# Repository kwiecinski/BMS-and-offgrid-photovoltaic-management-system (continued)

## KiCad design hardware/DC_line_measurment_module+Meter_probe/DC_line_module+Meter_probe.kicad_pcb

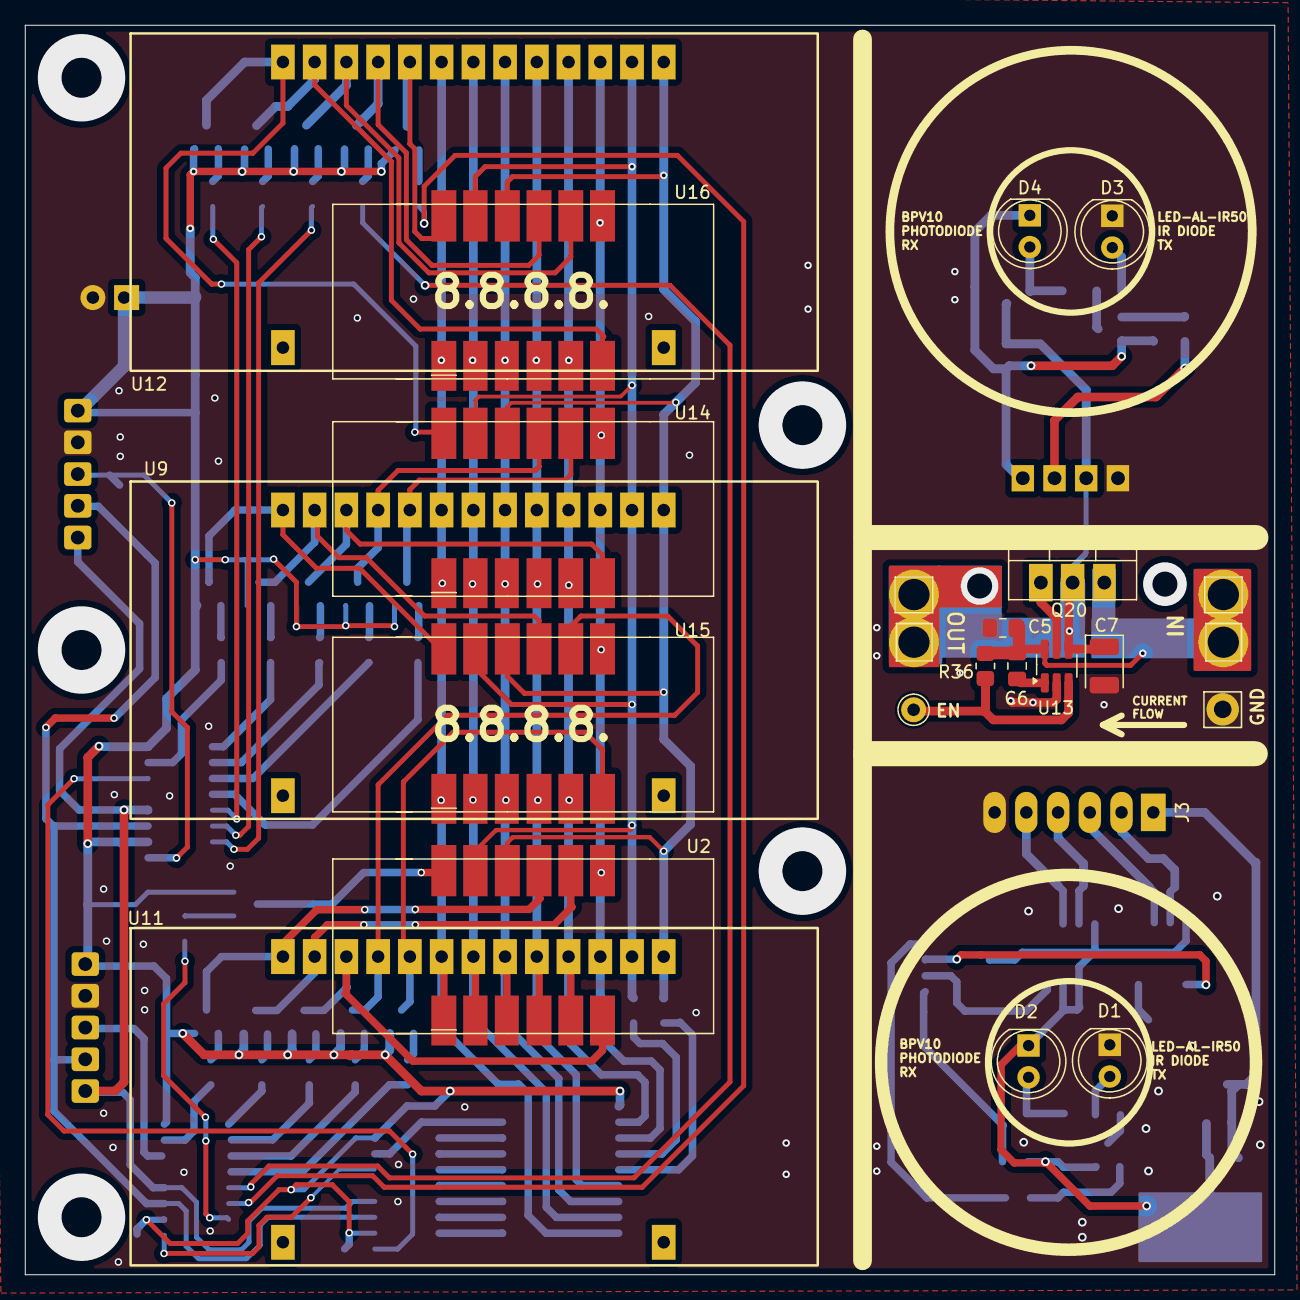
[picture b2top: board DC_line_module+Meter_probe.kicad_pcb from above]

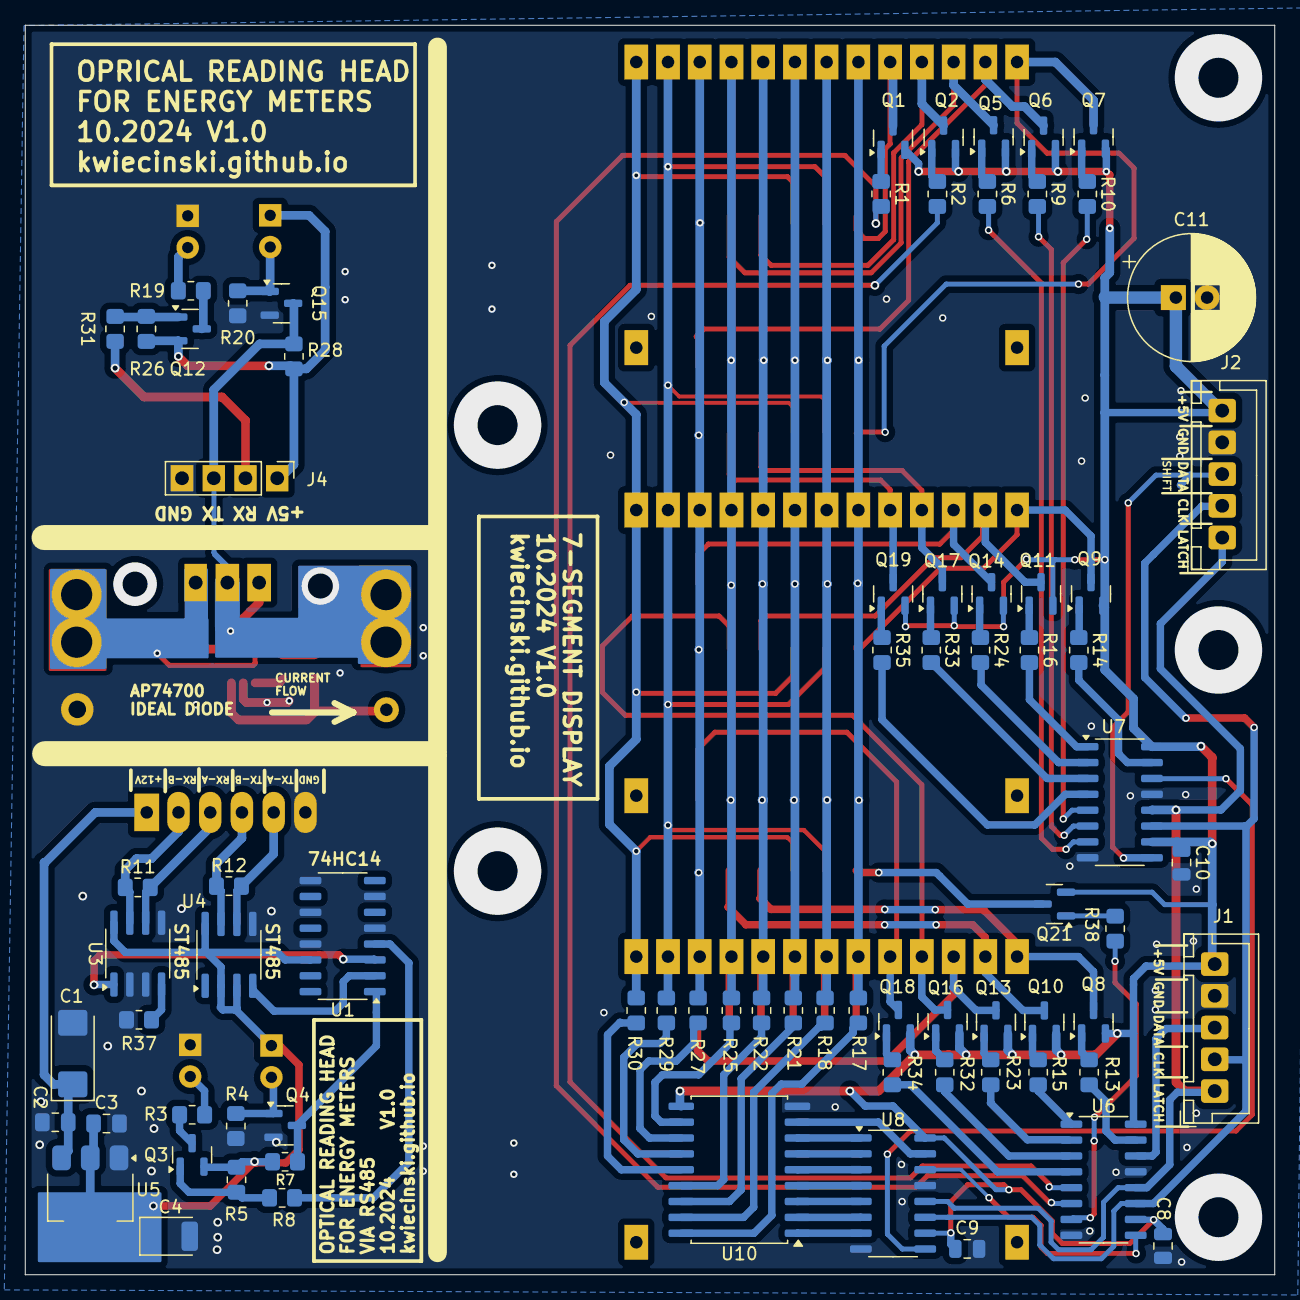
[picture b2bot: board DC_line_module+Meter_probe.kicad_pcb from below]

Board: 2 copper layers, 100.0 x 100.0 mm, 100 parts (76 on the bottom side), 106 nets.

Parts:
C1: 100u; CP_EIA-6032-28_Kemet-C
C2, C3, C5, C6: 100n; C_0805_2012Metric_Pad1.18x1.45mm_HandSolder
C4, C7: 22u; CP_EIA-3528-21_Kemet-B
C8, C9, C10: 100n; C_0805_2012Metric
C11: 470u/6,3V; CP_Radial_D10.0mm_P2.50mm
D1, D3: LED-AL-IR50; LED_D5.0mm
D2, D4: BPV10; LED_D5.0mm
J1: DATA_INPUT; JST_XH_B5B-XH-A_1x05_P2.54mm_Vertical
J2: DATA_BRIDGE; JST_XH_B5B-XH-A_1x05_P2.54mm_Vertical
J3: POWER_RS485; Pin_Header_Straight_1x06_Pitch2.54mm
J4: PROBE_CONN; PinHeader_1x04_P2.54mm_Vertical
J5, J5#2: IN; Pin_D1.4mm_L8.5mm_W2.8mm_FlatFork
J6: GND; Pin_D1.4mm_L8.5mm_W2.8mm_FlatFork
J7: GND; Pin_D1.0mm_L10.0mm
J8, J8#2: OUT; Pin_D1.4mm_L8.5mm_W2.8mm_FlatFork
Q1, Q2, Q3, Q5, Q6, Q7, Q8, Q9, Q10, Q11, Q12, Q13, Q14, Q16, Q17, Q18, Q19, Q21: BC807; SOT-23
Q4, Q15: BC817; SOT-23
Q20: IRF540N; TO-220-3_Vertical
R1, R2, R6, R9, R15, R16, R23, R24, R32, R33, R34, R35, R38: 10k; R_0805_2012Metric_Pad1.20x1.40mm_HandSolder
R3, R19: 160R; R_0805_2012Metric_Pad1.20x1.40mm_HandSolder
R4, R5, R20, R26: 47k; R_0805_2012Metric_Pad1.20x1.40mm_HandSolder
R7, R28: 22k; R_0805_2012Metric_Pad1.20x1.40mm_HandSolder
R8, R31, R36: 1k; R_0805_2012Metric_Pad1.20x1.40mm_HandSolder
R10, R13, R14, R37: 10K; R_0805_2012Metric_Pad1.20x1.40mm_HandSolder
R11, R12: 120R; R_0805_2012Metric_Pad1.20x1.40mm_HandSolder
R17, R18, R21, R22, R25, R27, R29, R30: 200R; R_0805_2012Metric_Pad1.20x1.40mm_HandSolder
U1: 74HC14; SO-16_3.9x9.9mm_P1.27mm
U2, U14, U15, U16: CA56-12SURKWA; 4-digit-7-segment-display_smd
U3, U4: ST485EBDR; SOIC-8_3.9x4.9mm_P1.27mm
U5: AMS1117-5.0; SOT-223-3_TabPin2
U6, U7, U8: 74HC595; SO-16_3.9x9.9mm_P1.27mm
U9, U11, U12: JZG_E5627BRG-1_7_SEGMENT_DISPLAY
U10: ULN2803A; SOIC-18W_7.5x11.6mm_P1.27mm
U13: AP74700; SOT-23-6_Handsoldering

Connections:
+5V: C3.1, C4.1, C8.1, C9.1, C10.1, C11.1, D2.1 (K), J1.5, J2.5, Q1.2 (E), Q2.2 (E), Q3.2 (E), Q5.2 (E), Q6.2 (E), Q7.2 (E), Q8.2 (E), Q9.2 (E), Q10.2 (E), Q11.2 (E), Q13.2 (E), Q14.2 (E), Q16.2 (E), Q17.2 (E), Q18.2 (E), Q19.2 (E), Q21.2 (E), R5.2, R7.1, U1.14 (VCC), U3.8 (VCC), U4.2 (~RE), U4.3 (DE), U4.8 (VCC), U5.2 (VO), U6.10 (~SRCLR), U6.16 (VCC), U7.10 (~SRCLR), U7.16 (VCC), U8.10 (~SRCLR), U8.16 (VCC), U10.10 (COM)
+5V_B: D4.1 (K), J4.1, Q12.2 (E), R26.2, R28.1
+12V: C1.1, C2.1, J3.1, U5.3 (VI)
/Energy meter probe/METER_RX: U1.3, U3.1 (RO)
/Energy meter probe/METER_RX_B: J4.2, R31.2
/Energy meter probe/METER_TX: U1.2, U4.4 (DI)
/Energy meter probe/METER_TX_B: J4.3, Q15.3 (C), R28.2
CLK: J1.2, J2.2, U6.11 (SRCLK), U7.11 (SRCLK), U8.11 (SRCLK)
DATA: J1.3, U6.14 (SER)
DISP1_A1: Q9.3 (C), U9.1 (A1), U15.12 (CA1)
DISP1_A2: Q11.3 (C), U9.2 (A2), U15.9 (CA2)
DISP1_A3: Q14.3 (C), U9.3 (A3), U14.6 (CA4)
DISP1_A4: Q17.3 (C), U9.4 (A4), U14.9 (CA2)
DISP1_A5: Q19.3 (C), U9.5 (A5), U14.8 (CA3)
DISP2_A1: Q8.3 (C), U2.9 (CA2), U11.1 (A1)
DISP2_A2: Q10.3 (C), U2.8 (CA3), U11.2 (A2)
DISP2_A3: Q13.3 (C), U2.6 (CA4), U11.3 (A3)
DISP2_A4: Q16.3 (C), U11.4 (A4), U15.8 (CA3)
DISP2_A5: Q18.3 (C), U11.5 (A5), U15.6 (CA4)
DISP3_A1: Q7.3 (C), U12.1 (A1), U14.12 (CA1)
DISP3_A2: Q6.3 (C), U12.2 (A2), U16.6 (CA4)
DISP3_A3: Q5.3 (C), U12.3 (A3), U16.8 (CA3)
DISP3_A4: Q2.3 (C), U12.4 (A4), U16.9 (CA2)
DISP3_A5: Q1.3 (C), U12.5 (A5), U16.12 (CA1)
DISP4_A1: Q21.3 (C), U2.12 (CA1)
DISP_A: R30.2, U2.10 (f), U9.13 (A), U11.13 (A), U12.13 (A), U14.10 (f), U15.10 (f), U16.10 (f)
DISP_B: R29.2, U2.11 (a), U9.12 (B), U11.12 (B), U12.12 (B), U14.11 (a), U15.11 (a), U16.11 (a)
DISP_C: R27.2, U2.7 (b), U9.11 (C), U11.11 (C), U12.11 (C), U14.7 (b), U15.7 (b), U16.7 (b)
DISP_D: R22.2, U2.4 (c), U9.9 (D), U11.9 (D), U12.9 (D), U14.4 (c), U15.4 (c), U16.4 (c)
DISP_DP: R25.2, U2.5 (g), U9.10 (Px), U11.10 (Px), U12.10 (Px), U14.5 (g), U15.5 (g), U16.5 (g)
DISP_E: R21.2, U2.3 (DPX), U9.8 (E), U11.8 (E), U12.8 (E), U14.3 (DPX), U15.3 (DPX), U16.3 (DPX)
DISP_F: R18.2, U2.2 (d), U9.7 (F), U11.7 (F), U12.7 (F), U14.2 (d), U15.2 (d), U16.2 (d)
DISP_G: R17.2, U2.1 (e), U9.6 (G), U11.6 (G), U12.6 (G), U14.1 (e), U15.1 (e), U16.1 (e)
GND: C1.2, C2.2, C3.2, C4.2, C5.2, C7.2, C8.2, C9.2, C10.2, C11.2, D1.1 (K), D3.1 (K), J1.4, J2.4, J3.6, J4.4, J6.1, Q4.2 (E), Q15.2 (E), R4.2, R20.2, R37.1, U1.5, U1.7 (GND), U1.9, U1.11, U1.13, U3.2 (~RE), U3.3 (DE), U3.5 (GND), U4.5 (GND), U5.1 (GND), U6.8 (GND), U6.13 (~OE), U7.8 (GND), U7.13 (~OE), U8.8 (GND), U8.13 (~OE), U10.9 (GND), U13.2 (GND)
LATCH: J1.1, J2.1, U6.12 (RCLK), U7.12 (RCLK), U8.12 (RCLK)
unnamed: D1.2 (A), R3.2
unnamed: D2.2 (A), Q4.1 (B), R4.1
unnamed: D3.2 (A), R19.2
unnamed: D4.2 (A), Q15.1 (B), R20.1
unnamed: J3.2, R11.1, U3.7 (B)
unnamed: J3.3, R11.2, U3.6 (A)
unnamed: J3.4, R12.1, U4.7 (B)
unnamed: J3.5, R12.2, U4.6 (A)
unnamed: C5.1, C6.1, J5.1, J5#2.1, Q20.3 (S), R36.2, U13.6 (ANODE)
unnamed: J7.1, R36.1, U13.3 (EN)
unnamed: C7.1, J8.1, J8#2.1, Q20.2 (D), U13.4 (CATHODE)
unnamed: Q1.1 (B), R1.1
unnamed: Q2.1 (B), R2.1
unnamed: Q3.1 (B), R5.1, R8.1
unnamed: Q3.3 (C), R3.1
unnamed: Q4.3 (C), R7.2, U1.1
unnamed: Q5.1 (B), R6.1
unnamed: Q6.1 (B), R9.1
unnamed: Q7.1 (B), R10.1
unnamed: Q8.1 (B), R13.1
unnamed: Q9.1 (B), R14.1
unnamed: Q10.1 (B), R15.1
unnamed: Q11.1 (B), R16.1
unnamed: Q12.1 (B), R26.1, R31.1
unnamed: Q12.3 (C), R19.1
unnamed: Q13.1 (B), R23.1
unnamed: Q14.1 (B), R24.1
unnamed: Q16.1 (B), R32.1
unnamed: Q17.1 (B), R33.1
unnamed: Q18.1 (B), R34.1
unnamed: Q19.1 (B), R35.1
unnamed: Q20.1 (G), U13.5 (GATE)
unnamed: Q21.1 (B), R38.1
unnamed: R8.2, U1.4
unnamed: R37.2, U3.4 (DI)
unnamed: R13.2, U6.15 (QA)
unnamed: R15.2, U6.1 (QB)
unnamed: R23.2, U6.2 (QC)
unnamed: R32.2, U6.3 (QD)
unnamed: R34.2, U6.4 (QE)
unnamed: U6.9 (QH'), U8.14 (SER)
unnamed: R38.2, U6.7 (QH)
unnamed: R14.2, U7.15 (QA)
unnamed: R16.2, U7.1 (QB)
unnamed: R24.2, U7.2 (QC)
unnamed: R33.2, U7.3 (QD)
unnamed: R35.2, U7.4 (QE)
unnamed: U7.14 (SER), U8.9 (QH')
unnamed: R17.1, U10.18 (O1)
unnamed: R18.1, U10.17 (O2)
unnamed: R21.1, U10.16 (O3)
unnamed: R22.1, U10.15 (O4)
unnamed: R30.1, U10.14 (O5)
unnamed: R29.1, U10.13 (O6)
unnamed: R27.1, U10.12 (O7)
unnamed: R25.1, U10.11 (O8)
unnamed: C6.2, U13.1 (VCP)
O2: R9.2, U7.6 (QG)
O3: R10.2, U7.5 (QF)
O4: R2.2, U6.5 (QF)
O5: R1.2, U6.6 (QG)
O6: R6.2, U7.7 (QH)
QA: U8.15 (QA), U10.8 (I8)
QB: U8.1 (QB), U10.7 (I7)
QC: U8.2 (QC), U10.6 (I6)
QD: U8.3 (QD), U10.5 (I5)
QE: U8.4 (QE), U10.4 (I4)
QF: U8.5 (QF), U10.3 (I3)
QG: U8.6 (QG), U10.2 (I2)
QH: U8.7 (QH), U10.1 (I1)
SHIFTED_DATA: J2.3, U7.9 (QH')

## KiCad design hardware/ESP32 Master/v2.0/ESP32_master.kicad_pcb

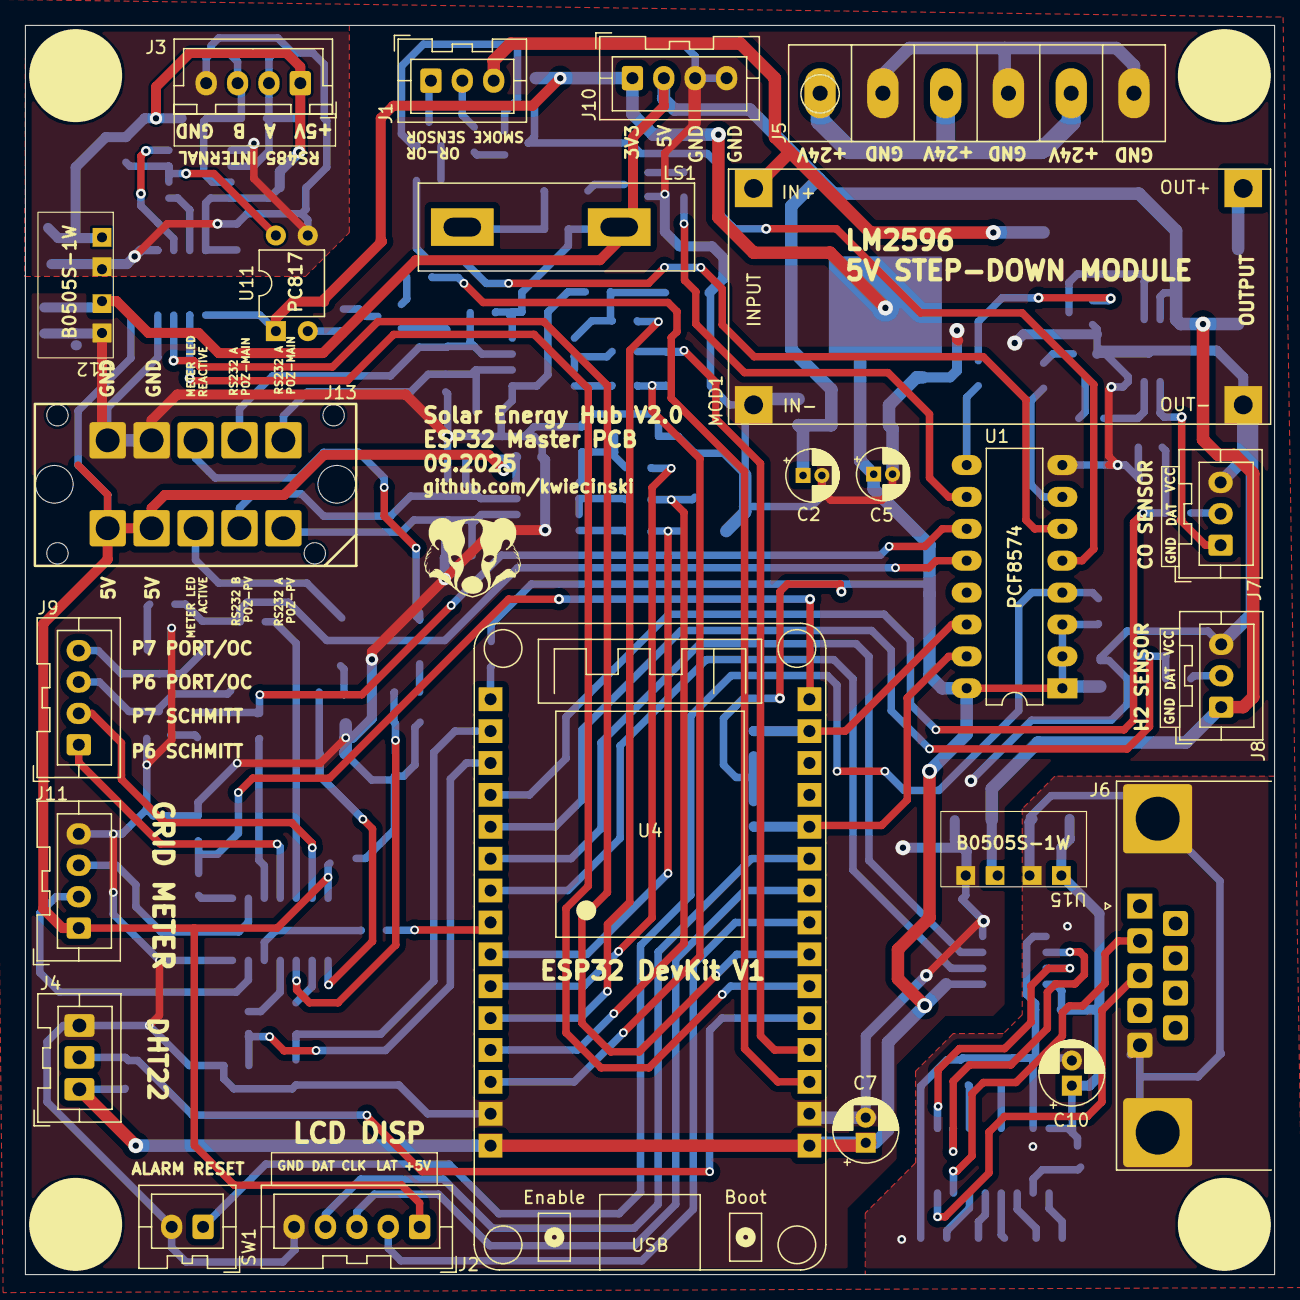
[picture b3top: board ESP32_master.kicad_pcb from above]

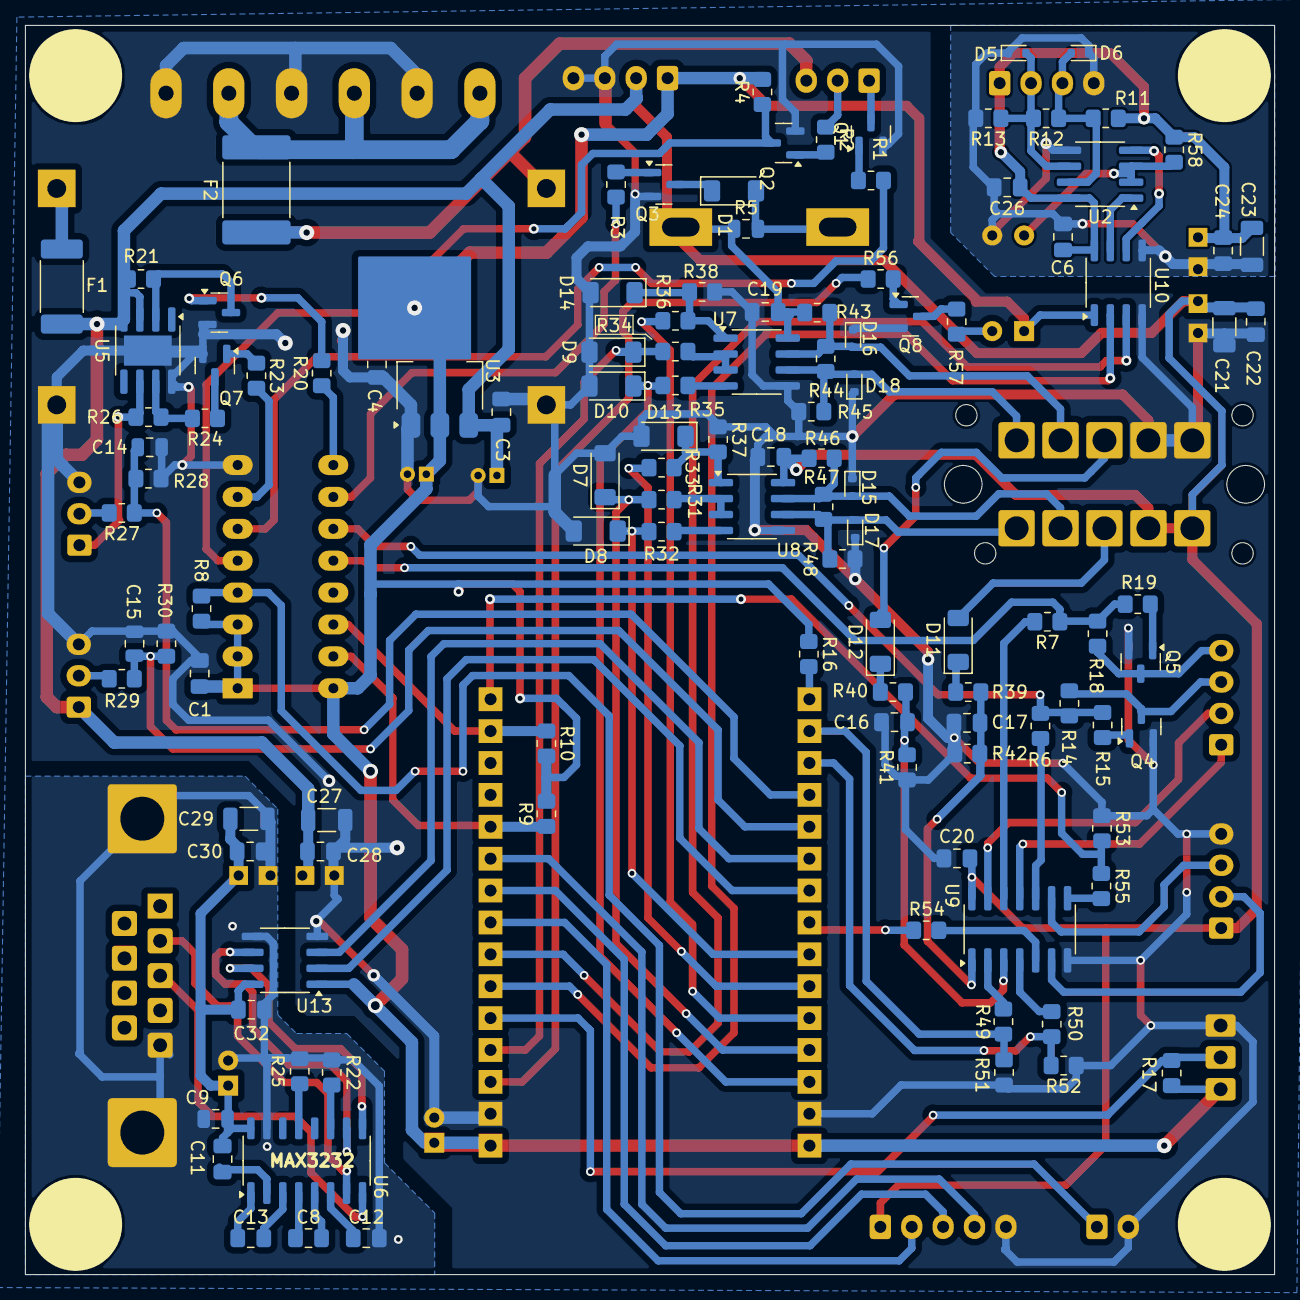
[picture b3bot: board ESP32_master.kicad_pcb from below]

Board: 2 copper layers, 99.5 x 99.5 mm, 146 parts (118 on the bottom side), 107 nets.

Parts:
C1, C3, C4, C6, C8, C11, C12, C13, C16, C17, C18, C19, C20, C22, C24, C26, C28, C30, C32: 100n; C_0805_2012Metric_Pad1.18x1.45mm_HandSolder
C2: 100u; CP_Radial_D4.0mm_P1.50mm
C5: 22u; CP_Radial_D4.0mm_P1.50mm
C7: 22u; CP_Radial_D5.0mm_P2.00mm
C9: 100n; C_0805_2012Metric
C10: 47u; CP_Radial_D5.0mm_P2.00mm
C14, C15: 10n; C_0805_2012Metric
C21, C23, C27, C29: 10u; C_1206_3216Metric
D1: 1N4148; D_MiniMELF
D5, D6, D15, D16, D17, D18: LESD5D5.0CT1G-MS; D_SOD-523
D7, D8, D9, D10, D13, D14: BZV55B3V6; D_MiniMELF
D11, D12: LL4148; D_MiniMELF
F1: 2A; Fuse_2512_6332Metric_Pad1.52x3.35mm_HandSolder
F2: Polyfuse; Fuse_2920_7451Metric
H1, H2, H3, H4: MountingHole; Mount-Hole-3mm
J1: OR-OR SMOKE SENSOR; JST_XA_B03B-XASK-1_1x03_P2.50mm_Vertical
J2: LCD_DISP; JST_XA_B05B-XASK-1_1x05_P2.50mm_Vertical
J3: RS485; JST_XH_B4B-XH-A_1x04_P2.50mm_Vertical
J4: DHT22; JST_XA_1x03_P2.54mm_Vertical
J5: DC_LINE_OUTPUT; Screw-Terminal-P6-rast-5mm-6,7x30
J6: DB9_Socket; DSUB-9_Female_Horizontal_P2.77x2.84mm_EdgePinOffset7.70mm_H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
J7: CO_SENSOR; JST_XA_B03B-XASK-1_1x03_P2.50mm_Vertical
J8: H2_SENSOR; JST_XA_B03B-XASK-1_1x03_P2.50mm_Vertical
J9, J10: Unconnected; JST_XA_B04B-XASK-1_1x04_P2.50mm_Vertical
J11: METER_GRID; JST_XA_B04B-XASK-1_1x04_P2.50mm_Vertical
J13: METER_INTERFACES; CDDC-1,5-5-PV-3,5
LS1: BUZZER; Buzzer
MOD1: LM2596-Step-Down; LM2596-Step-Down-Conv
Q1, Q2, Q3, Q4, Q5, Q8: BC817; SOT-23
Q6, Q7: BSS138; SOT-23
R1, R2, R3, R4, R8, R9, R10, R16, R17, R21, R37, R38, R51, R52, R53: 10k; R_0805_2012Metric_Pad1.20x1.40mm_HandSolder
R5: 2k; C_0805_2012Metric
R6, R7, R14, R18: 0R; R_0805_2012Metric_Pad1.20x1.40mm_HandSolder
R11, R13, R22, R25, R39, R40, R43, R45, R46, R48, R56, R57: 1k; R_0805_2012Metric_Pad1.20x1.40mm_HandSolder
R12, R44, R47: 120R; R_0805_2012Metric_Pad1.20x1.40mm_HandSolder
R15, R19, R26: 10K; R_0805_2012Metric_Pad1.20x1.40mm_HandSolder
R20, R23: 100R; R_0805_2012Metric_Pad1.20x1.40mm_HandSolder
R24: 1k8; R_0805_2012Metric_Pad1.20x1.40mm_HandSolder
R27, R29: 7k8; R_0805_2012Metric_Pad1.20x1.40mm_HandSolder
R28, R30: 2k2; R_0805_2012Metric_Pad1.20x1.40mm_HandSolder
R31, R32, R34, R35, R54, R58: 4k7; R_0805_2012Metric_Pad1.20x1.40mm_HandSolder
R33, R36, R49, R50, R55: 4k7/5k1; R_0805_2012Metric_Pad1.20x1.40mm_HandSolder
R41, R42: 100K; R_0805_2012Metric_Pad1.20x1.40mm_HandSolder
SW1: SW_Push; JST_XA_B02B-XASK-1_1x02_P2.50mm_Vertical
U1: PCF8574; DIP-16_W7.62mm_LongPads
U2: ST485; SOIC-8_3.9x4.9mm_P1.27mm
U3: AMS1117-5.0; SOT-223-3_TabPin2
U4: ESP32_DevKit_V1_DOIT; esp32_devkit_v1_doit
U5: UP7760; SOIC-8-1EP_3.9x4.9mm_P1.27mm_EP2.41x3.81mm
U6: MAX3232; SO-16_3.9x9.9mm_P1.27mm
U7, U8: ST485EBDR; SOIC-8_3.9x4.9mm_P1.27mm
U9: 74HC14; SOIC-14_3.9x8.7mm_P1.27mm
U10, U13: ADUM3211ARZ; SO-8_3.9x4.9mm_P1.27mm
U11: PC817; DIP-4_W7.62mm
U12, U15: B0505S-1W; B0505S

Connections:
+3V3: C1.1, C4.1, C5.1, C7.1, J4.1, J10.1, R4.2, R8.2, R9.2, R10.2, R16.1, R17.2, U1.1 (A0), U1.2 (A1), U1.3 (A2), U1.16 (VDD), U3.2 (VO), U4.15 (VIN), U4.16 (3V3), U10.1 (VDD1), U11.1, U13.1 (VDD1)
+5V: C2.1, C3.1, C18.1, C19.1, C20.1, C21.1, C22.1, C27.1, C28.1, F1.2, J2.1, J8.1, J10.2, J11.1, J13.4, J13.5, LS1.- (2), R5.1, R21.2, R43.2, R46.2, U3.3 (VI), U5.3 (VIN), U5.4 (CNTL), U7.8 (VCC), U8.8 (VCC), U9.14 (VCC), U12.2 (VIN), U15.2 (VIN)
+5V_INV: C9.2, C10.1, C11.1, C29.1, C30.1, C32.1, U6.16 (VCC), U13.8 (VDD2), U15.4 (VOUT)
+5V_RS485: C6.1, C23.1, C24.1, C26.1, J3.1, R11.1, R58.1, U2.8 (VCC), U10.8 (VDD2), U12.4 (VOUT)
+24V: F2.1, J1.3, MOD1.2 (IN+)
/ESP32_Measurment_Board/INV_RX_RS232: J6.2, U6.7 (T2OUT)
/ESP32_Measurment_Board/INV_TX_RS232: J6.3, U6.8 (R2IN)
/ESP32_Measurment_Board/RS485_A: D5.2 (A2), J3.2, R12.2, R13.1, U2.6 (A)
/ESP32_Measurment_Board/RS485_B: D6.2 (A2), J3.3, R11.2, R12.1, U2.7 (B)
ALARM_RESET_BUTTON: R8.1, SW1.1, U1.4 (P0)
BUZZER: R3.1, U1.10 (P5)
CLOCK_ESP: R10.1, U1.14 (SCL), U4.29 (IO22)
CO_SENSOR_EN: R20.2, U1.9 (P4)
CO_SENSOR_SWITCH_VOLTAGES: R23.2, U1.7 (P3)
DHT22: J4.2, R17.1, U4.20 (IO4)
GAMA_METER_LED_ACTIVE_ENERGY: R49.1, R51.2, U4.2 (SENSOR_VP)
GAMA_METER_LED_ACTIVE_ENERGY_INPUT: D11.2 (A), J13.3
GAMA_METER_LED_REACTIVE: R50.1, R52.2, U4.3 (SENSOR_VN)
GAMA_METER_LED_REACTIVE_INPUT: D12.2 (A), J13.8
GND: C1.2, C2.2, C3.2, C4.2, C5.2, C7.2, C14.1, C15.1, C16.2, C17.2, C18.2, C19.2, C20.2, C21.2, C22.2, C27.2, C28.2, D7.2 (A), D8.2 (A), D9.2 (A), D10.2 (A), D13.2 (A), D14.2 (A), D15.1 (A1), D16.1 (A1), D17.1 (A1), D18.1 (A1), J2.5, J4.3, J5.2, J5.4, J5.6, J7.3, J8.3, J10.3, J10.4, J11.4, J13.6, J13.7, MOD1.1 (IN-), MOD1.3 (OUT-), Q1.2 (E), Q2.2 (E), Q3.2 (E), Q4.2 (E), Q5.2 (E), Q6.2 (S), Q7.2 (S), Q8.2 (E), R28.1, R30.1, R37.1, R38.1, R41.1, R42.1, R45.1, R48.1, R51.1, R52.1, R53.1, SW1.2, U1.8 (VSS), U3.1 (GND), U4.14 (GND), U4.17 (GND), U5.8 (GND), U5.9 (EP), U7.5 (GND), U8.5 (GND), U9.7 (GND), U10.4 (GND1), U12.1 (GND), U13.4 (GND1), U15.1 (GND)
GND_INV: C9.1, C10.2, C12.2, C29.2, C30.2, C32.2, J6.5, R22.2, R25.1, U6.15 (GND), U13.5 (GND2), U15.3 (0V)
GND_RS485: C6.2, C23.2, C24.2, C26.2, D5.1 (A1), D6.1 (A1), J3.4, R13.2, U2.5 (GND), U10.5 (GND2), U11.3, U12.3 (0V)
INVERTER_RX: U4.7 (IO33), U13.2 (VOA)
INVERTER_TX: U4.6 (IO32), U13.3 (VIB)
LCD_DISP_CLOCK: J2.3, U4.24 (IO18)
LCD_DISP_DATA: J2.4, U4.25 (IO19)
LCD_DISP_LATCH: J2.2, U4.23 (IO5)
METER_GRID_RX: R53.2, R55.1, U4.30 (IO23)
METER_GRID_TX: R54.1, U4.8 (IO25)
METER_MAIN_A: D18.2 (A2), J13.10, R44.1, R45.2, U7.6 (A)
METER_MAIN_B: D16.2 (A2), J13.9, R43.1, R44.2, U7.7 (B)
METER_MAIN_DIR: D9.1 (K), R34.1, U4.19 (IO2)
METER_MAIN_RX: D10.1 (K), R35.1, U4.13 (IO13)
METER_MAIN_TX: R36.1, U4.11 (IO14)
METER_PV_A: D17.2 (A2), J13.1, R47.1, R48.2, U8.6 (A)
METER_PV_B: D15.2 (A2), J13.2, R46.1, R47.2, U8.7 (B)
METER_PV_DIR: D7.1 (K), R31.1, U4.12 (IO12)
METER_PV_RX: D8.1 (K), R32.1, U4.9 (IO26)
METER_PV_TX: R33.1, U4.10 (IO27)
MQ7_CO_SENSOR: C14.2, R27.1, R28.2, U4.4 (IO34)
MQ8_H2_SENSOR: C15.2, R29.1, R30.2, U4.5 (IO35)
unnamed: C16.1, R40.2, R41.2, U9.3
unnamed: C17.1, R39.2, R42.2, U9.1
unnamed: D1.2 (A), LS1.+ (1), R5.2
unnamed: D1.1 (K), Q3.3 (C)
unnamed: D11.1 (K), R39.1
unnamed: D12.1 (K), R40.1
unnamed: D13.1 (K), R33.2, R37.2, U8.1 (RO)
unnamed: D14.1 (K), R36.2, R38.2, U7.1 (RO)
unnamed: J1.1, Q1.3 (C)
unnamed: J1.2, R2.1
unnamed: F2.2, J5.1, J5.3, J5.5
unnamed: J7.1, R26.1, U5.6 (VOUT)
unnamed: J7.2, R27.2
unnamed: J8.2, R29.2
unnamed: J9.1, U9.11
unnamed: J9.2, U9.13
unnamed: J9.3, Q4.3 (C), R14.1
unnamed: J9.4, Q5.3 (C), R18.1
unnamed: J11.2, U9.6
unnamed: J11.3, U9.9
unnamed: F1.1, MOD1.4 (OUT+)
unnamed: Q1.1 (B), R1.2
unnamed: Q2.1 (B), R2.2
unnamed: Q3.1 (B), R3.2
unnamed: Q4.1 (B), R15.1
unnamed: Q5.1 (B), R19.1
unnamed: Q6.3 (D), R21.1, U5.2 (EN)
unnamed: Q6.1 (G), R20.1
unnamed: Q7.3 (D), R24.1
unnamed: Q7.1 (G), R23.1
unnamed: Q8.1 (B), R56.2
unnamed: Q8.3 (C), R57.1
unnamed: R6.2, U9.10
unnamed: R7.2, U9.12
unnamed: R49.2, U9.2
unnamed: R50.2, U9.4
unnamed: R54.2, U9.5
unnamed: R55.2, U9.8
unnamed: R57.2, U11.2
unnamed: R58.2, U2.2 (~RE), U2.3 (DE), U11.4
unnamed: R16.2, U4.1 (EN)
unnamed: R24.2, R26.2, U5.7 (FB)
unnamed: C13.1, U6.1 (C1+)
unnamed: C13.2, U6.3 (C1-)
unnamed: C8.1, U6.4 (C2+)
unnamed: C8.2, U6.5 (C2-)
unnamed: R25.2, U6.13 (R1IN)
unnamed: R22.1, U6.11 (T1IN)
unnamed: C11.2, U6.2 (VS+)
unnamed: C12.1, U6.6 (VS-)
unnamed: R34.2, U7.2 (~RE), U7.3 (DE)
unnamed: R35.2, U7.4 (DI)
unnamed: R31.2, U8.2 (~RE), U8.3 (DE)
unnamed: R32.2, U8.4 (DI)
unnamed: U2.1 (RO), U10.7 (VIA)
unnamed: U2.4 (DI), U10.6 (VOB)
unnamed: U6.9 (R2OUT), U13.7 (VIA)
unnamed: U6.10 (T2IN), U13.6 (VOB)
P6_UNCONNECTED: R6.1, R14.2, R15.2, U1.11 (P6)
P7_UNCONNECTED: R7.1, R18.2, R19.2, U1.12 (P7)
RS485_DIR: R56.1, U4.18 (IO15)
RS485_RX_ESP: U4.21 (IO16), U10.2 (VOA)
RS485_TX_ESP: U4.22 (IO17), U10.3 (VIB)
SDA_ESP: R9.1, U1.15 (SDA), U4.26 (IO21)
SMOKE_DETECTOR: Q2.3 (C), R4.1, U1.5 (P1)
SMOKE_DETECTOR_RESET: R1.1, U1.6 (P2)
